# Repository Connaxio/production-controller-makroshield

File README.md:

# Production Controller makroShield
The Production Controller makroShield (PCM) is a modular controller designed to operate 24 V devices with the help of connected and remote sensors.

The PCM has a mikroBUS socket that works with Espoir, our Power over Ethernet devboard, to provide remote control, as well as advanced functionalities through node-red and Home Assistant. Simpler control can be achieved by directly programming Espoir.

Originally designed to operate greenhouses and irrigation valves, it can be adapted to many different kinds of small productions and climate control due to its modular nature.

2 drivers are available with the PCM: a 2-ways driver for bidirectional motors, and a 1-way, AC/DC controller for other devices, like valves, fans, and unidirectional motors. Up to 15 drivers can be connected simultaneously, and scheduled to use up to 350 Watts of power at a time.

Being modular makes the PCM easy to repair and upgrade, and helps reduce cost for smaller operations.

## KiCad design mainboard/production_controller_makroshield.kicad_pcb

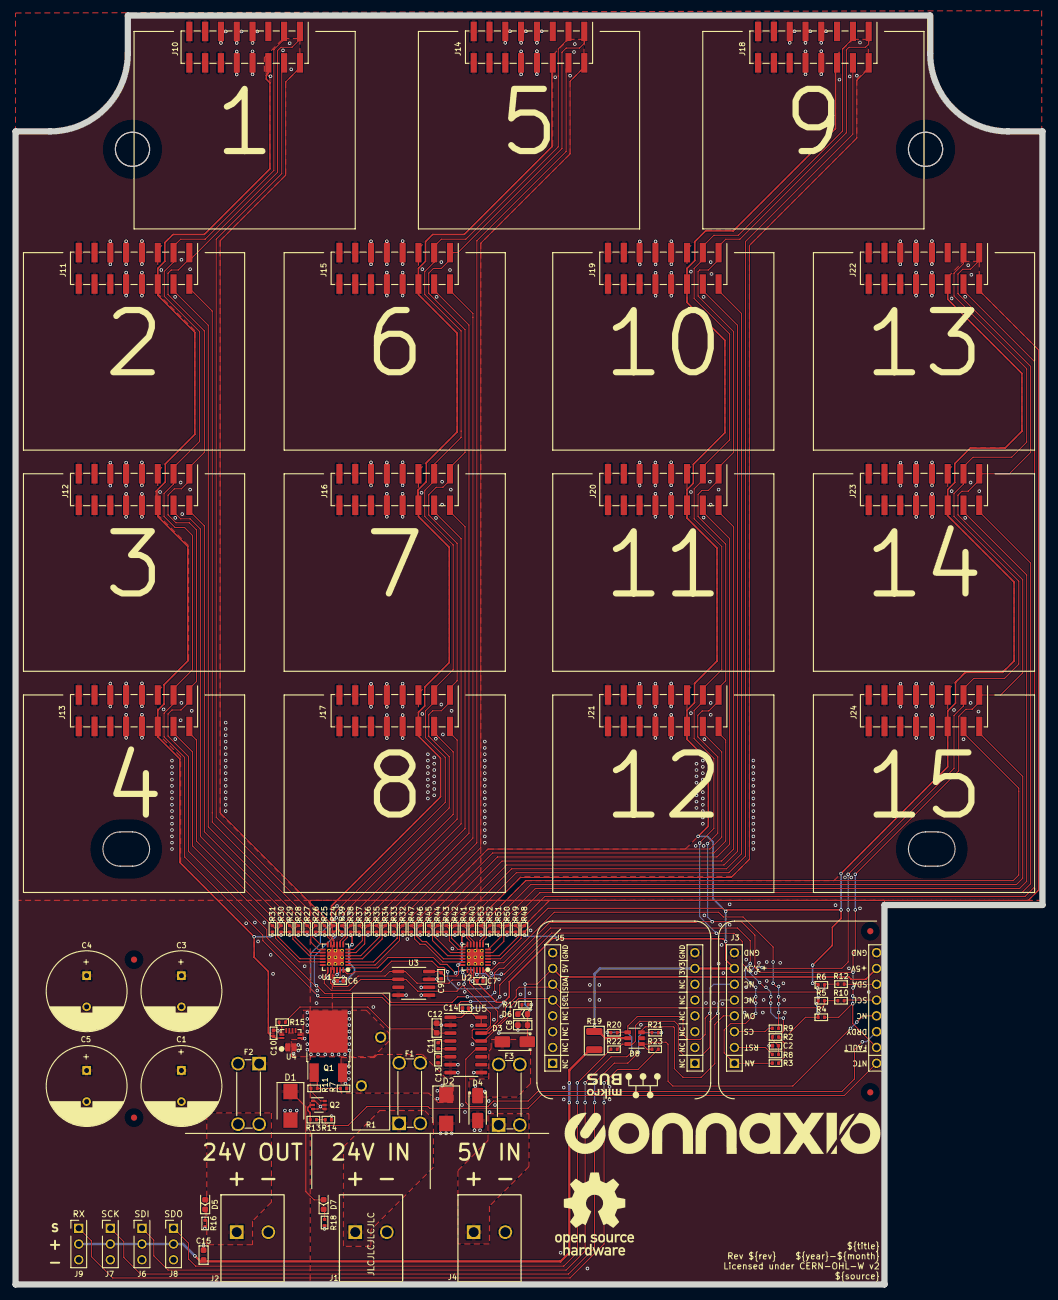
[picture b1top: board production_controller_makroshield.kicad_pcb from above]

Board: 2 copper layers, 165.1 x 204.0 mm, 118 parts (1 on the bottom side), 72 nets.

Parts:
C1, C3, C4, C5: CAP_AE_1MF_50V_TH_12.5MM; CAPAE_RAD_D12.5_H26.5_P5
C2, C6, C7, C9, C10, C11, C13, C14: CAP_CER_100NF_25V_0402; CAP_CER_0402_1005M
C8, C12, C15: CAP_CER_22UF_10V_0603; CAP_CER_0603_1608M
D1, D2: DIO_TVS_24V_UNI_SMB; DO-124AA_SMB
D3: DIO_SBD_100V_3A_SMA; DO-214AC_SMA
D4: DIO_TVS_5V_UNI_SMA; DO-214AC_SMA
D5, D6, D7: DIO_LED_GREEN_150060GS75000; LED_0603_1608M
D8: DIO_TVS_SRV05-4HTG; SOT-23-6
F1, F2, F3: FUS_BLADE_MINI_3588-1
F4, F5, F6, F7: FID_1X3
J1, J2, J4: CON_TERM_BLK_1X2_TB008A-508-02BE
J3: CON_HDR_MIKROBUS_ADDON_TH
J5: CON_HDR_MIKROBUS_SOCKET_TH
J6, J7, J8, J9: CON_HDR_100MILS_M_TH_1X3
J10, J11, J12, J13, J14, J15, J16, J17, J18, J19, J20, J21, J22, J23, J24: CON_CONNAXIO_MOTOR_DRIVER
MTH1, MTH2: MTH_M5_NPTH
MTH3, MTH4: MTH_SLOT_M5_2MM_NPTH
Q1: TRX_PMOS_AOD4189; TO-252-3
Q2: TRX_2NPN_BC846S,115; SOT-363_SC-70-6
R1: NTC_SL22 2R018; RV_DISC_D22_W6_P7.8
R2, R3, R4, R7, R11, R13, R14, R24, R25, R26, R27, R28, R29, R30, R31, R32, R33, R34, R35, R36, R37, R38, R39, R40, R41, R42, R43, R44, R45, R46, R47, R48, R49, R50, R51, R52, R53: RES_12.4KΩ_1%_0402; RES_0402_1005M
R5, R6, R15, R16, R18: RES_5.10KΩ_1%_0402; RES_0402_1005M
R8, R9, R10, R12, R20, R21, R22, R23: RES_226Ω_1%_0402; RES_0402_1005M
R17: RES_1.00KΩ_1%_0402; RES_0402_1005M
R19: PTC_SMD1210B010TF; RES_1210_3225M
U1, U2: IO_EXP_PI4IOE5V6416ZDEX; QFN-24_4x4_P0.5_EP2.7X2.7
U3: SEN_TEMP_TMP1075DR; SOIC-8_3.9x4.9_P1.27
U4: SEN_CUR_ACS711KEXLT-31AB-T; QFN-12_CUR_SEN_ACS7
U5: ADC_NAU7802SGI; SOIC-16_3.9X9.9_P1.27

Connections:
+3.3V: C6.1, C7.1, C9.1, C10.1, C14.1, D8.5, J3.7 (+3.3V), J5.7 (+3.3V), J10.6 (3.3V), J11.6 (3.3V), J12.6 (3.3V), J13.6 (3.3V), J14.6 (3.3V), J15.6 (3.3V), J16.6 (3.3V), J17.6 (3.3V), J18.6 (3.3V), J19.6 (3.3V), J20.6 (3.3V), J21.6 (3.3V), J22.6 (3.3V), J23.6 (3.3V), J24.6 (3.3V), R2.1, R3.1, R4.1, R5.1, R6.1, R19.1, R24.1, R25.1, R26.1, R27.1, R28.1, R29.1, R30.1, R31.1, R32.1, R33.1, R34.1, R35.1, R36.1, R37.1, R38.1, R39.1, R40.1, R41.1, R42.1, R43.1, R44.1, R45.1, R46.1, R47.1, R48.1, R49.1, R50.1, R51.1, R52.1, R53.1, U1.21 (VDDP), U1.23 (VDDI2C), U2.18 (ADDR), U2.21 (VDDP), U2.23 (VDDI2C), U3.8 (V+), U4.12 (VCC), U5.1 (REFP), U5.15 (DVDD), U5.16 (AVDD)
+5V: C8.1, D3.1 (K), D6.2 (A), J3.15 (+5V), J5.15 (+5V)
+24VDC: C1.1, C3.1, C4.1, C5.1, D1.1 (K), D7.2 (A), F2.1, F2.2, J10.12 (VDrive), J10.13 (VDrive), J10.14 (VDrive), J10.15 (VDrive), J10.16 (VDrive), J11.12 (VDrive), J11.13 (VDrive), J11.14 (VDrive), J11.15 (VDrive), J11.16 (VDrive), J12.12 (VDrive), J12.13 (VDrive), J12.14 (VDrive), J12.15 (VDrive), J12.16 (VDrive), J13.12 (VDrive), J13.13 (VDrive), J13.14 (VDrive), J13.15 (VDrive), J13.16 (VDrive), J14.12 (VDrive), J14.13 (VDrive), J14.14 (VDrive), J14.15 (VDrive), J14.16 (VDrive), J15.12 (VDrive), J15.13 (VDrive), J15.14 (VDrive), J15.15 (VDrive), J15.16 (VDrive), J16.12 (VDrive), J16.13 (VDrive), J16.14 (VDrive), J16.15 (VDrive), J16.16 (VDrive), J17.12 (VDrive), J17.13 (VDrive), J17.14 (VDrive), J17.15 (VDrive), J17.16 (VDrive), J18.12 (VDrive), J18.13 (VDrive), J18.14 (VDrive), J18.15 (VDrive), J18.16 (VDrive), J19.12 (VDrive), J19.13 (VDrive), J19.14 (VDrive), J19.15 (VDrive), J19.16 (VDrive), J20.12 (VDrive), J20.13 (VDrive), J20.14 (VDrive), J20.15 (VDrive), J20.16 (VDrive), J21.12 (VDrive), J21.13 (VDrive), J21.14 (VDrive), J21.15 (VDrive), J21.16 (VDrive), J22.12 (VDrive), J22.13 (VDrive), J22.14 (VDrive), J22.15 (VDrive), J22.16 (VDrive), J23.12 (VDrive), J23.13 (VDrive), J23.14 (VDrive), J23.15 (VDrive), J23.16 (VDrive), J24.12 (VDrive), J24.13 (VDrive), J24.14 (VDrive), J24.15 (VDrive), J24.16 (VDrive), U4.1 (IP+), U4.2 (IP+)
/24V_OUT: D5.2 (A), F2.3, F2.4, J2.1
/CS+: Q1.3 (D), R1.2, U4.3 (IP-), U4.4 (IP-)
/DRDY: J3.11 (TX), U5.12 (DRDY)
/I2C_SCL: J5.13 (SCL), R5.2, R10.2, U1.19 (SCL), U2.19 (SCL), U3.2 (SCL), U5.13 (SCLK)
/I2C_SDA: J5.14 (SDA), R6.2, R12.2, U1.20 (SDA), U2.20 (SDA), U3.1 (SDA), U5.14 (SDIO)
/INT_IO: J3.1 (AN), R3.2, U1.22 (~INT), U2.22 (~INT)
/IO_RX: D8.1, J3.12 (RX), R23.1
/IO_SCK: D8.3, J3.4 (SCK), R21.1
/IO_SDI: D8.4, J3.6 (SDI), R20.1
/IO_SDO: D8.6, J3.5 (SDO), R22.1
/NTC_BYPASS: J3.9 (PWM), R13.1, R14.1
/RST_IO: R9.1, U1.24 (~RESET), U2.24 (~RESET)
CTRLA1: J10.2 (~CTRLA), R24.2, U1.10 (P1_0)
CTRLA2: J11.2 (~CTRLA), R26.2, U1.12 (P1_2)
CTRLA3: J12.2 (~CTRLA), R28.2, U1.14 (P1_4)
CTRLA4: J13.2 (~CTRLA), R30.2, U1.16 (P1_6)
CTRLA5: J14.2 (~CTRLA), R32.2, U1.1 (P0_0)
CTRLA6: J15.2 (~CTRLA), R34.2, U1.3 (P0_2)
CTRLA7: J16.2 (~CTRLA), R36.2, U1.5 (P0_4)
CTRLA8: J17.2 (~CTRLA), R38.2, U1.7 (P0_6)
CTRLA9: J18.2 (~CTRLA), R40.2, U2.10 (P1_0)
CTRLA10: J19.2 (~CTRLA), R42.2, U2.12 (P1_2)
CTRLA11: J20.2 (~CTRLA), R44.2, U2.14 (P1_4)
CTRLA12: J21.2 (~CTRLA), R46.2, U2.16 (P1_6)
CTRLA13: J22.2 (~CTRLA), R48.2, U2.3 (P0_2)
CTRLA14: J23.2 (~CTRLA), R50.2, U2.5 (P0_4)
CTRLA15: J24.2 (~CTRLA), R52.2, U2.7 (P0_6)
CTRLB1: J10.4 (~CTRLB), R25.2, U1.11 (P1_1)
CTRLB2: J11.4 (~CTRLB), R27.2, U1.13 (P1_3)
CTRLB3: J12.4 (~CTRLB), R29.2, U1.15 (P1_5)
CTRLB4: J13.4 (~CTRLB), R31.2, U1.17 (P1_7)
CTRLB5: J14.4 (~CTRLB), R33.2, U1.2 (P0_1)
CTRLB6: J15.4 (~CTRLB), R35.2, U1.4 (P0_3)
CTRLB7: J16.4 (~CTRLB), R37.2, U1.6 (P0_5)
CTRLB8: J17.4 (~CTRLB), R39.2, U1.8 (P0_7)
CTRLB9: J18.4 (~CTRLB), R41.2, U2.11 (P1_1)
CTRLB10: J19.4 (~CTRLB), R43.2, U2.13 (P1_3)
CTRLB11: J20.4 (~CTRLB), R45.2, U2.15 (P1_5)
CTRLB12: J21.4 (~CTRLB), R47.2, U2.17 (P1_7)
CTRLB13: J22.4 (~CTRLB), R49.2, U2.4 (P0_3)
CTRLB14: J23.4 (~CTRLB), R51.2, U2.6 (P0_5)
CTRLB15: J24.4 (~CTRLB), R53.2, U2.8 (P0_7)
FAULT: J3.10 (INT), J10.1 (~FAULT), J11.1 (~FAULT), J12.1 (~FAULT), J13.1 (~FAULT), J14.1 (~FAULT), J15.1 (~FAULT), J16.1 (~FAULT), J17.1 (~FAULT), J18.1 (~FAULT), J19.1 (~FAULT), J20.1 (~FAULT), J21.1 (~FAULT), J22.1 (~FAULT), J23.1 (~FAULT), J24.1 (~FAULT), R4.2
GND: C1.2, C2.2, C3.2, C4.2, C5.2, C6.2, C7.2, C8.2, C9.2, C10.2, C12.2, C13.2, C14.2, C15.2, D1.2 (A), D2.2 (A), D4.2 (A), D8.2, J1.2, J2.2, J3.8 (GND), J3.16 (GND), J4.2, J5.8 (GND), J5.16 (GND), J6.3, J7.3, J8.3, J9.3, J10.7 (GND), J10.8 (GND), J10.9 (GND), J10.10 (GND), J10.11 (GND), J11.7 (GND), J11.8 (GND), J11.9 (GND), J11.10 (GND), J11.11 (GND), J12.7 (GND), J12.8 (GND), J12.9 (GND), J12.10 (GND), J12.11 (GND), J13.7 (GND), J13.8 (GND), J13.9 (GND), J13.10 (GND), J13.11 (GND), J14.7 (GND), J14.8 (GND), J14.9 (GND), J14.10 (GND), J14.11 (GND), J15.7 (GND), J15.8 (GND), J15.9 (GND), J15.10 (GND), J15.11 (GND), J16.7 (GND), J16.8 (GND), J16.9 (GND), J16.10 (GND), J16.11 (GND), J17.7 (GND), J17.8 (GND), J17.9 (GND), J17.10 (GND), J17.11 (GND), J18.7 (GND), J18.8 (GND), J18.9 (GND), J18.10 (GND), J18.11 (GND), J19.7 (GND), J19.8 (GND), J19.9 (GND), J19.10 (GND), J19.11 (GND), J20.7 (GND), J20.8 (GND), J20.9 (GND), J20.10 (GND), J20.11 (GND), J21.7 (GND), J21.8 (GND), J21.9 (GND), J21.10 (GND), J21.11 (GND), J22.7 (GND), J22.8 (GND), J22.9 (GND), J22.10 (GND), J22.11 (GND), J23.7 (GND), J23.8 (GND), J23.9 (GND), J23.10 (GND), J23.11 (GND), J24.7 (GND), J24.8 (GND), J24.9 (GND), J24.10 (GND), J24.11 (GND), Q2.1 (E1), Q2.3 (C2), Q2.4 (E2), Q2.5 (B2), R14.2, R16.2, R17.2, R18.2, U1.9 (VSS), U1.18 (ADDR), U1.25 (PAD), U2.9 (VSS), U2.25 (PAD), U3.4 (GND), U3.5 (A2), U3.6 (A1), U3.7 (A0), U4.5 (GND), U5.2 (VIN1N), U5.7 (REFN), U5.8 (AVSS), U5.9 (DVSS)
unnamed: C11.1, U5.5 (VIN2P)
unnamed: C11.2, U5.4 (VIN2N)
unnamed: C12.1, R15.2, U5.3 (VIN1P)
unnamed: C13.1, U5.6 (VBG)
unnamed: D2.1 (K), F1.3, F1.4, Q1.2 (S), R1.1, R7.1
unnamed: D3.2 (A), D4.1 (K), F3.3, F3.4
unnamed: D5.1 (K), R16.1
unnamed: D6.1 (K), R17.1
unnamed: D7.1 (K), R18.1
unnamed: F1.1, F1.2, J1.1
unnamed: F3.1, F3.2, J4.1
unnamed: J3.2 (RST), R8.2
unnamed: J3.3 (CS), R9.2
unnamed: J3.13 (SCL), R10.1
unnamed: J3.14 (SDA), R12.1
unnamed: J6.1, R20.2
unnamed: J7.1, R21.2
unnamed: J8.1, R22.2
unnamed: C15.1, J6.2, J7.2, J8.2, J9.2, R19.2
unnamed: J9.1, R23.2
unnamed: Q1.1 (G), R7.2, R11.1
unnamed: Q2.2 (B1), R13.2
unnamed: Q2.6 (C1), R11.2
unnamed: R15.1, U4.11 (VIOUT)
RST_MOT: C2.1, J10.3 (~RESET), J11.3 (~RESET), J12.3 (~RESET), J13.3 (~RESET), J14.3 (~RESET), J15.3 (~RESET), J16.3 (~RESET), J17.3 (~RESET), J18.3 (~RESET), J19.3 (~RESET), J20.3 (~RESET), J21.3 (~RESET), J22.3 (~RESET), J23.3 (~RESET), J24.3 (~RESET), R2.2, R8.1

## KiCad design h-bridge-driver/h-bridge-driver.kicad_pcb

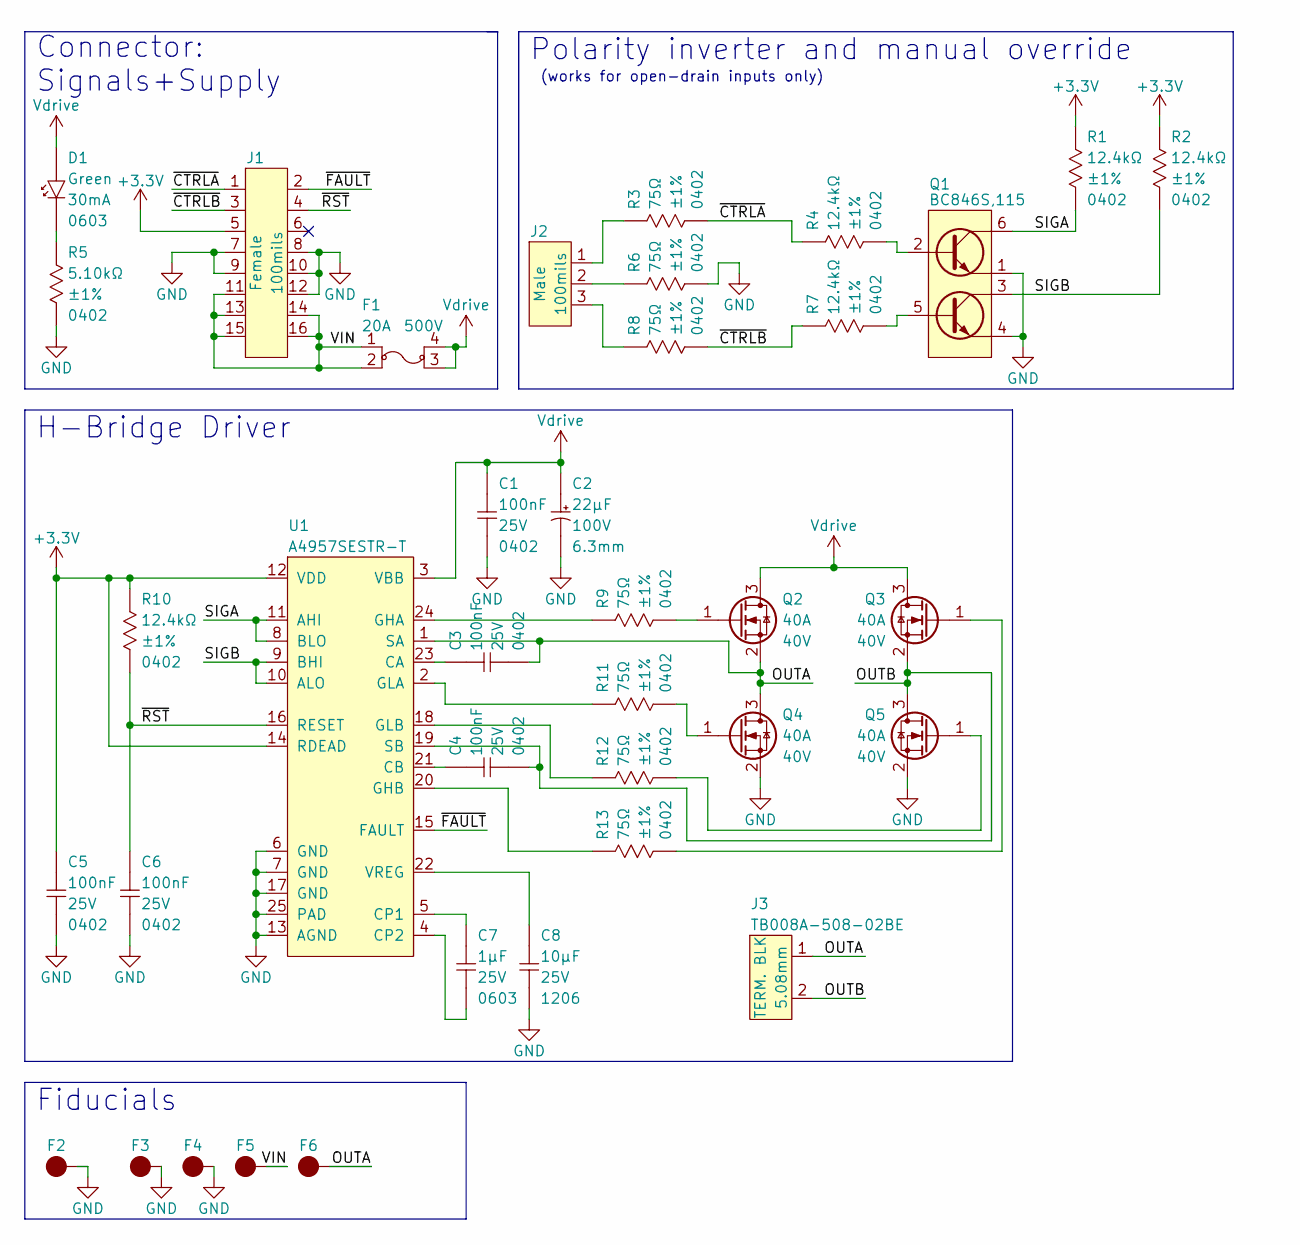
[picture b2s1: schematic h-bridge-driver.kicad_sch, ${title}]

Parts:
C1, C3, C4, C5, C6: CAP_CER_100NF_25V_0402; CAP_CER_0402_1005M; Tolerance ±10%; Voltage 25V; Manufacturer Part Number CL05A104KA5NNNC
C2: CAP_AE_22UF_100V_TH_6.3MM; CAP_AE_RAD_D6.3_H12.5_P2.5; Tolerance ±20%; Voltage 100V; Manufacturer Part Number ESK226M100AE3AA
C7: CAP_CER_1UF_25V_0603; CAP_CER_0603_1608M; Tolerance ±10%; Voltage 25V; Manufacturer Part Number CL10A105KA8NNNC
C8: CAP_CER_10UF_25V_1206; CAP_CER_1206_3216M; Tolerance ±10%; Voltage 25V; Manufacturer Part Number CL31A106KAHNNNE
D1: DIO_LED_GREEN_150060GS75000; LED_0603_1608M; Manufacturer Part Number 150060GS75000
F1: FUS_BLADE_MINI_3588-1; Voltage 500V; Manufacturer Part Number 3588-1
F2, F3, F4, F5, F6: FID_1X1
J1: CON_HDR_100MILS_F_TH_2X8; Voltage 350V
J2: CON_HDR_100MILS_M_TH_1X3; Voltage 350V
J3: CON_TERM_BLK_1X2_TB008A-508-02BE; Voltage 300V; Manufacturer Part Number TB008A-508-02BE
Q1: TRX_2NPN_BC846S,115; SOT-363_SC-70-6; Voltage 65V; Manufacturer Part Number BC846S,115
Q2, Q3, Q4, Q5: TRX_NMOS_PJD40N04_L2_00001; TO-252-3; Voltage 40V; Manufacturer Part Number PJD40N04_L2_00001
R1, R2, R4, R7, R10: RES_12.4KΩ_1%_0402; RES_0402_1005M; Tolerance ±1%; Voltage 50V; Manufacturer Part Number RMCF0402FT12K4
R3, R6, R8, R9, R11, R12, R13: RES_226Ω_1%_0402; RES_0402_1005M; Tolerance ±1%; Voltage 50V; Manufacturer Part Number RMCF0402FT75R0
R5: RES_5.10KΩ_1%_0402; RES_0402_1005M; Tolerance ±1%; Voltage 50V; Manufacturer Part Number RMCF0402FT5K10
U1: DRV_A4957SESTR-T; QFN-24_4x4_P0.5_EP2.7X2.7; Voltage 50V; Manufacturer Part Number A4957SESTR-T

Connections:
+3.3V: C5.1, J1.5, R1.1, R2.1, R10.1, U1.12 (VDD), U1.14 (RDEAD)
/OUTA: C3.2, F6.1, J3.1, Q2.2 (S), Q4.3 (D), U1.1 (SA)
/OUTB: C4.2, J3.2, Q3.2 (S), Q5.3 (D), U1.19 (SB)
/SIGA: Q1.6 (C1), R1.2, U1.8 (BLO), U1.11 (AHI)
/SIGB: Q1.3 (C2), R2.2, U1.9 (BHI), U1.10 (ALO)
/VIN: F1.1, F1.2, F5.1, J1.11, J1.13, J1.14, J1.15, J1.16
/~CTRLA: J1.1, R3.2, R4.1
/~CTRLB: J1.3, R7.1, R8.2
/~FAULT: J1.2, U1.15 (FAULT)
/~RST: C6.1, J1.4, R10.2, U1.16 (RESET)
GND: C1.2, C2.2, C5.2, C6.2, C8.2, F2.1, F3.1, F4.1, J1.7, J1.8, J1.9, J1.10, J1.12, Q1.1 (E1), Q1.4 (E2), Q4.2 (S), Q5.2 (S), R5.2, R6.2, U1.6 (GND), U1.7 (GND), U1.13 (AGND), U1.17 (GND), U1.25 (PAD)
unnamed: C3.1, U1.23 (CA)
unnamed: C4.1, U1.21 (CB)
unnamed: C7.1, U1.5 (CP1)
unnamed: C7.2, U1.4 (CP2)
unnamed: C8.1, U1.22 (VREG)
unnamed: D1.1 (K), R5.1
unnamed: J2.1, R3.1
unnamed: J2.2, R6.1
unnamed: J2.3, R8.1
unnamed: Q1.2 (B1), R4.2
unnamed: Q1.5 (B2), R7.2
unnamed: Q2.1 (G), R9.2
unnamed: Q3.1 (G), R13.2
unnamed: Q4.1 (G), R11.2
unnamed: Q5.1 (G), R12.2
unnamed: R9.1, U1.24 (GHA)
unnamed: R11.1, U1.2 (GLA)
unnamed: R12.1, U1.18 (GLB)
unnamed: R13.1, U1.20 (GHB)
Vdrive: C1.1, C2.1, D1.2 (A), F1.3, F1.4, Q2.3 (D), Q3.3 (D), U1.3 (VBB)

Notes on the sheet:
Fiducials
Polarity inverter and manual override
H-Bridge Driver
Connector: Signals+Supply
(works for open-drain inputs only)

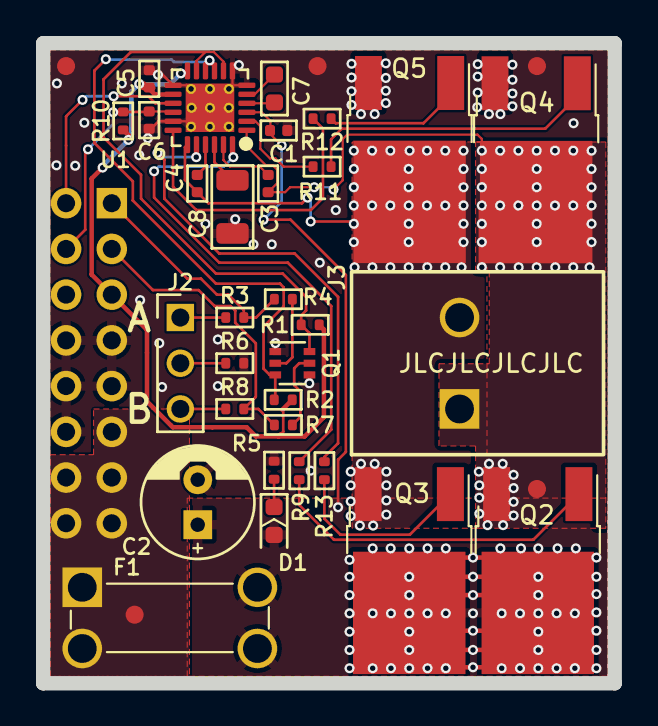
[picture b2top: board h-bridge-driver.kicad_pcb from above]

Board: 2 copper layers, 31.8 x 35.6 mm, 37 parts (1 on the bottom side), 31 nets.

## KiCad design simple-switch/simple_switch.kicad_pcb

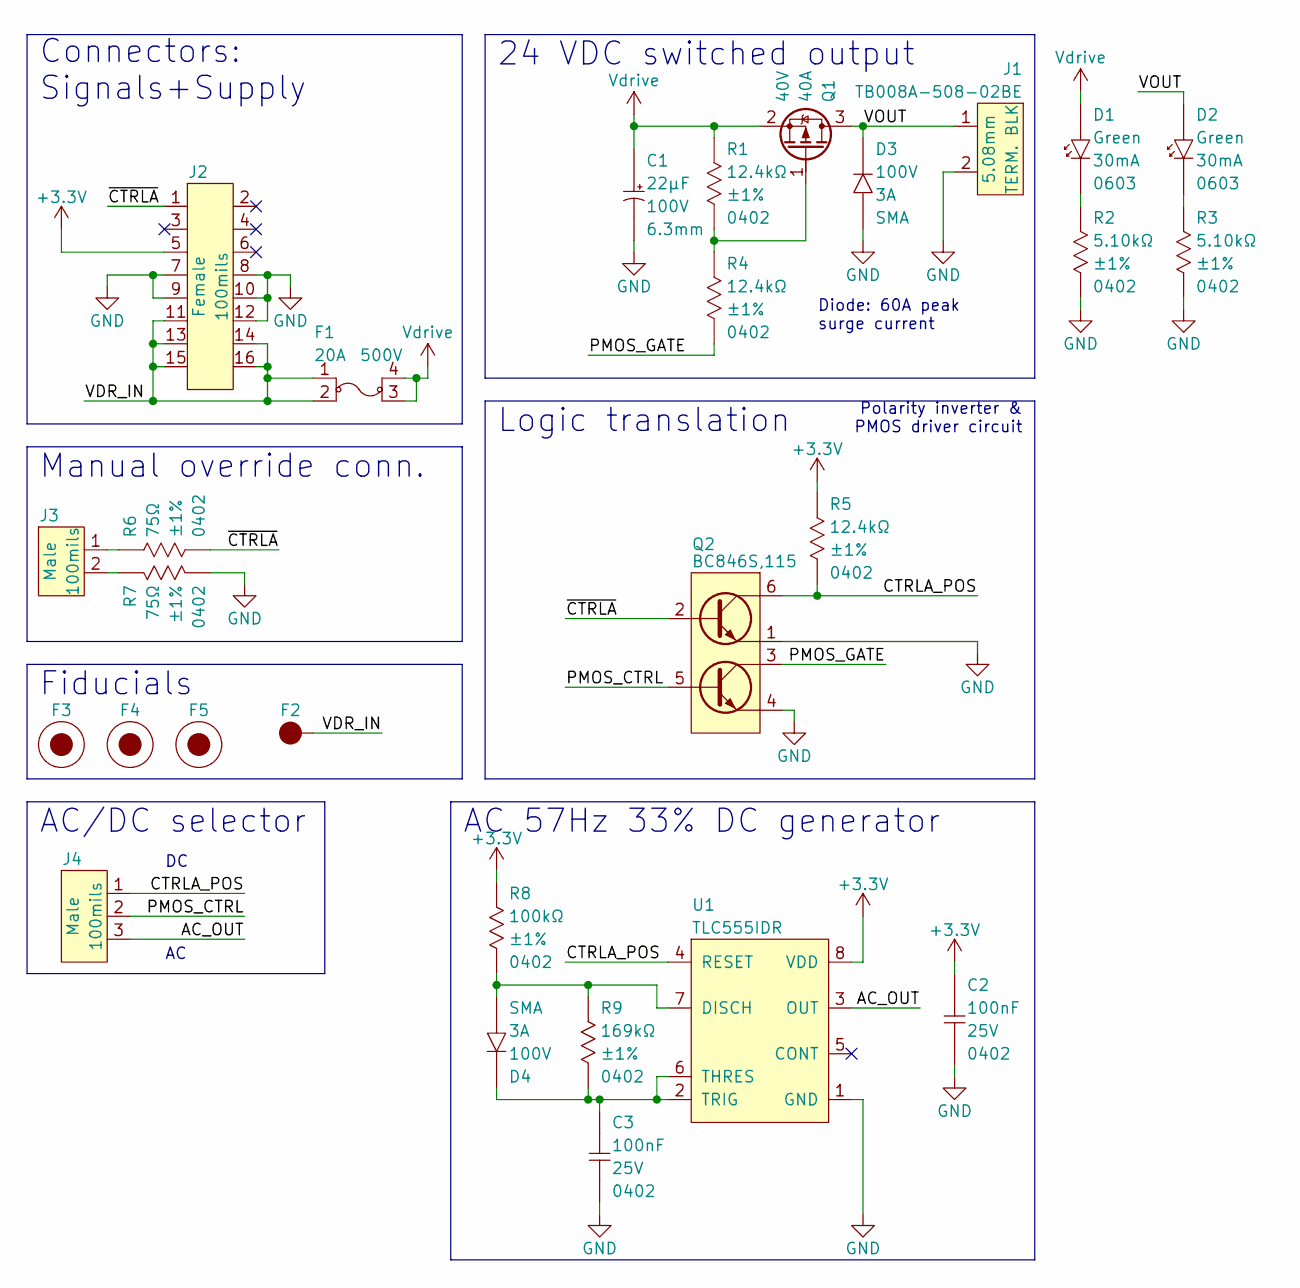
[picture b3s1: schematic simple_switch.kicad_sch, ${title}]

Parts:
C1: CAP_AE_22UF_100V_TH_6.3MM; CAP_AE_RAD_D6.3_H12.5_P2.5; Tolerance ±20%; Voltage 100V; Manufacturer Part Number ESK226M100AE3AA
C2, C3: CAP_CER_100NF_25V_0402; CAP_CER_0402_1005M; Tolerance ±10%; Voltage 25V; Manufacturer Part Number CL05A104KA5NNNC
D1, D2: DIO_LED_GREEN_150060GS75000; LED_0603_1608M; Manufacturer Part Number 150060GS75000
D3, D4: DIO_SBD_100V_3A_SMA; DO-214AC_SMA; Tolerance 60A; Voltage 100V; Manufacturer Part Number SL310A-TP
F1: FUS_BLADE_MINI_3588-1; Voltage 500V; Manufacturer Part Number 3588-1
F2: FID_1X1
F3, F4, F5: FID_1X3
J1: CON_TERM_BLK_1X2_TB008A-508-02BE; Voltage 300V; Manufacturer Part Number TB008A-508-02BE
J2: CON_HDR_100MILS_F_TH_2X8; Voltage 350V
J3: CON_HDR_100MILS_M_TH_1X2; Voltage 350V
J4: CON_HDR_100MILS_M_TH_1X3; Voltage 350V
Q1: TRX_PMOS_AOD4189; TO-252-3; Voltage 40V; Manufacturer Part Number AOD4189
Q2: TRX_2NPN_BC846S,115; SOT-363_SC-70-6; Voltage 65V; Manufacturer Part Number BC846S,115
R1, R4, R5: RES_12.4KΩ_1%_0402; RES_0402_1005M; Tolerance ±1%; Voltage 50V; Manufacturer Part Number RMCF0402FT12K4
R2, R3: RES_5.10KΩ_1%_0402; RES_0402_1005M; Tolerance ±1%; Voltage 50V; Manufacturer Part Number RMCF0402FT5K10
R6, R7: RES_226Ω_1%_0402; RES_0402_1005M; Tolerance ±1%; Voltage 50V; Manufacturer Part Number RMCF0402FT75R0
R8: RES_100KΩ_1%_0402; RES_0402_1005M; Tolerance ±1%; Voltage 50V; Manufacturer Part Number RMCF0402FT100K
R9: RES_169KΩ_1%_0402; RES_0402_1005M; Tolerance ±1%; Voltage 50V; Manufacturer Part Number RMCF0402FT169K
U1: TIMER_TLC555IDR; SOIC-8_3.9x4.9_P1.27; Voltage 3V - 15V; Manufacturer Part Number TLC555IDR

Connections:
+3.3V: C2.1, J2.5, R5.1, R8.1, U1.8 (VDD)
/AC_OUT: J4.3, U1.3 (OUT)
/CTRLA_POS: J4.1, Q2.6 (C1), R5.2, U1.4 (RESET)
/PMOS_CTRL: J4.2, Q2.5 (B2)
/PMOS_GATE: Q2.3 (C2), R4.2
/VDR_IN: F1.1, F1.2, F2.1, J2.11, J2.13, J2.14, J2.15, J2.16
/VOUT: D2.2 (A), D3.1 (K), J1.1, Q1.3 (D)
/~CTRLA: J2.1, Q2.2 (B1), R6.2
GND: C1.2, C2.2, C3.2, D3.2 (A), J1.2, J2.7, J2.8, J2.9, J2.10, J2.12, Q2.1 (E1), Q2.4 (E2), R2.2, R3.2, R7.2, U1.1 (GND)
unnamed: C3.1, D4.1 (K), R9.2, U1.2 (TRIG), U1.6 (THRES)
unnamed: D1.1 (K), R2.1
unnamed: D2.1 (K), R3.1
unnamed: D4.2 (A), R8.2, R9.1, U1.7 (DISCH)
unnamed: J3.1, R6.1
unnamed: J3.2, R7.1
unnamed: Q1.1 (G), R1.2, R4.1
Vdrive: C1.1, D1.2 (A), F1.3, F1.4, Q1.2 (S), R1.1

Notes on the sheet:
AC 57Hz 33% DC generator
Diode: 60A peak surge current
Polarity inverter & PMOS driver circuit
Logic translation
AC/DC selector
DC AC
Manual override conn.
Fiducials
24 VDC switched output
Connectors: Signals+Supply

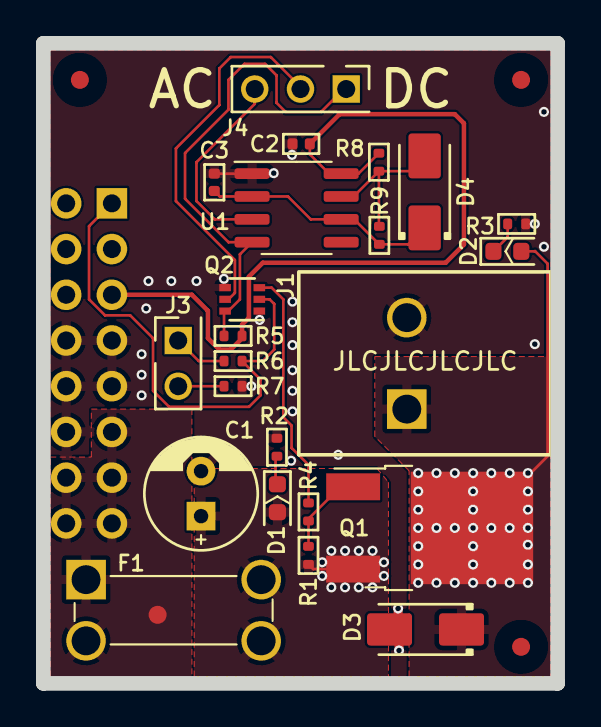
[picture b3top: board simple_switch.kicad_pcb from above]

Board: 2 copper layers, 28.6 x 35.6 mm, 28 parts (1 on the bottom side), 17 nets.

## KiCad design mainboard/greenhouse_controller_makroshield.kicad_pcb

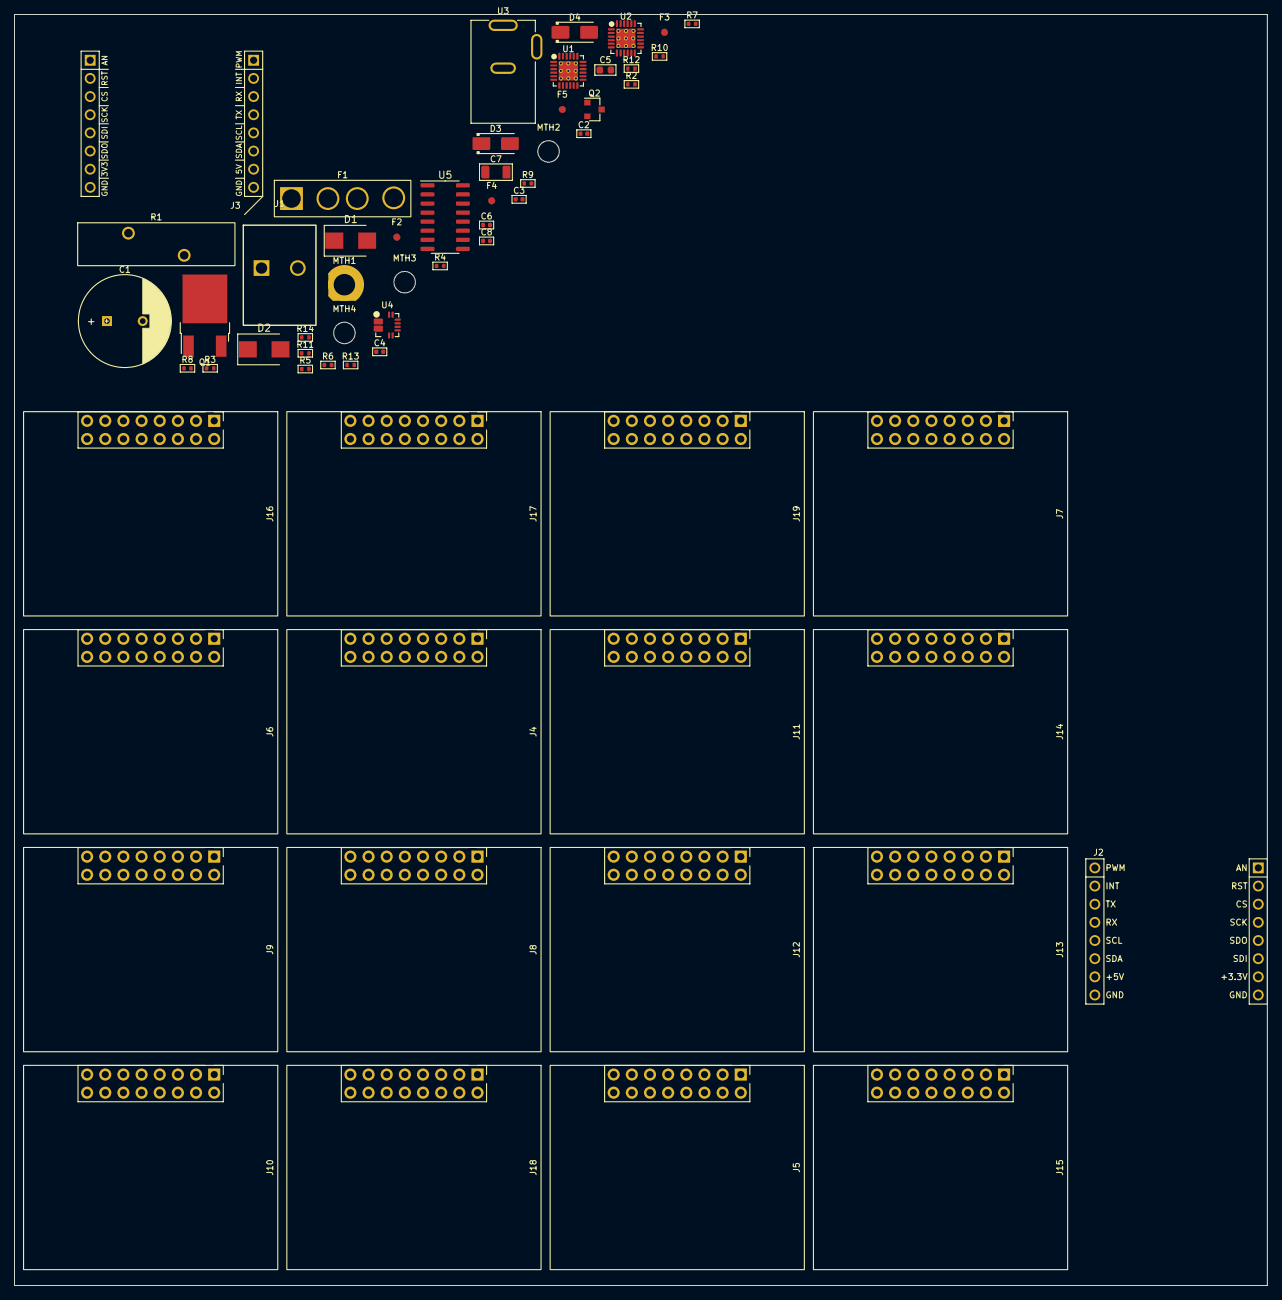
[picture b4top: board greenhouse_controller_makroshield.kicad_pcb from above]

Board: 2 copper layers, 175.3 x 177.8 mm, 61 parts (1 on the bottom side), 57 nets, no tracks yet.

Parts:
C1: CAP_AE_1MF_50V_TH_12.5MM; CAPAE_RAD_D12.5_H26.5_P5
C2, C3, C4, C6, C8: CAP_CER_100NF_25V_0402; CAP_CER_0402_1005M
C5: CAP_CER_22UF_10V_0603; CAP_CER_0603_1608M
C7: CAP_CER_10UF_25V_1206; CAP_CER_1206_3216M
D1, D2: DIO_TVS_24V_UNI_SMB; DO-124AA_SMB
D3: DIO_SBD_100V_3A_SMA; DO-214AC_SMA
D4: DIO_TVS_5V_UNI_SMA; DO-214AC_SMA
F1: FUS_BLADE_3522
F2, F3, F4, F5: FID_1X3
J1: CON_TERM_BLK_1X2_TB008A-508-02BE
J2: CON_HDR_MIKROBUS_ADDON_TH
J3: CON_HDR_MIKROBUS_SOCKET_TH
J4, J5, J6, J7, J8, J9, J10, J11, J12, J13, J14, J15, J16, J17, J18, J19: CON_CONNAXIO_MOTOR_DRIVER
MTH1: MTH_M2.5_PTH_CORNER
MTH2, MTH3, MTH4: MTH_M2.5_NPTH
Q1: TRX_PMOS_AOD4189; TO-252-3
Q2: TRX_NPN_MMBT3904-TP; SOT-23-3
R1: NTC_SL22 2R018; RV_DISC_D22_W6_P7.8
R2, R3, R4, R7, R10, R12, R14: RES_12.4KΩ_1%_0402; RES_0402_1005M
R5, R6, R11: RES_1.54KΩ_1%_0402; RES_0402_1005M
R8, R9: RES_226Ω_1%_0402; RES_0402_1005M
R13: RES_0Ω_0402; RES_0402_1005M
U1, U2: IO_EXP_PI4IOE5V6416ZDEX; QFN-24_4x4_P0.5_EP2.7X2.7
U3: CON_BARREL_2.1X5.5_PJ-002A
U4: SUN_CUR_ACS711KEXLT-31AB-T; QFN-12_CUR_SEN_ACS7
U5: ADC_NAU7802SGI; SOIC-16_3.9X9.9_P1.27

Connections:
+3.3V: C3.1, C4.1, C6.1, J2.7 (+3.3V), J3.7 (+3.3V), J4.6 (3.3V), J5.6 (3.3V), J6.6 (3.3V), J7.6 (3.3V), J8.6 (3.3V), J9.6 (3.3V), J10.6 (3.3V), J11.6 (3.3V), J12.6 (3.3V), J13.6 (3.3V), J14.6 (3.3V), J15.6 (3.3V), J16.6 (3.3V), J17.6 (3.3V), J18.6 (3.3V), J19.6 (3.3V), R2.1, R3.1, R4.1, R5.1, R6.1, U1.21 (VDDP), U1.23 (VDDI2C), U2.18 (ADDR), U2.21 (VDDP), U2.23 (VDDI2C), U4.12 (VCC), U5.1 (REFP), U5.15 (DVDD), U5.16 (AVDD)
+5V: C5.1, D3.1 (K), D4.1 (K), J2.15 (+5V), J3.15 (+5V)
+24VDC: C1.1, D1.1 (K), J4.12 (VDrive), J4.13 (VDrive), J4.14 (VDrive), J4.15 (VDrive), J4.16 (VDrive), J5.12 (VDrive), J5.13 (VDrive), J5.14 (VDrive), J5.15 (VDrive), J5.16 (VDrive), J6.12 (VDrive), J6.13 (VDrive), J6.14 (VDrive), J6.15 (VDrive), J6.16 (VDrive), J7.12 (VDrive), J7.13 (VDrive), J7.14 (VDrive), J7.15 (VDrive), J7.16 (VDrive), J8.12 (VDrive), J8.13 (VDrive), J8.14 (VDrive), J8.15 (VDrive), J8.16 (VDrive), J9.12 (VDrive), J9.13 (VDrive), J9.14 (VDrive), J9.15 (VDrive), J9.16 (VDrive), J10.12 (VDrive), J10.13 (VDrive), J10.14 (VDrive), J10.15 (VDrive), J10.16 (VDrive), J11.12 (VDrive), J11.13 (VDrive), J11.14 (VDrive), J11.15 (VDrive), J11.16 (VDrive), J12.12 (VDrive), J12.13 (VDrive), J12.14 (VDrive), J12.15 (VDrive), J12.16 (VDrive), J13.12 (VDrive), J13.13 (VDrive), J13.14 (VDrive), J13.15 (VDrive), J13.16 (VDrive), J14.12 (VDrive), J14.13 (VDrive), J14.14 (VDrive), J14.15 (VDrive), J14.16 (VDrive), J15.12 (VDrive), J15.13 (VDrive), J15.14 (VDrive), J15.15 (VDrive), J15.16 (VDrive), J16.12 (VDrive), J16.13 (VDrive), J16.14 (VDrive), J16.15 (VDrive), J16.16 (VDrive), J17.12 (VDrive), J17.13 (VDrive), J17.14 (VDrive), J17.15 (VDrive), J17.16 (VDrive), J18.12 (VDrive), J18.13 (VDrive), J18.14 (VDrive), J18.15 (VDrive), J18.16 (VDrive), J19.12 (VDrive), J19.13 (VDrive), J19.14 (VDrive), J19.15 (VDrive), J19.16 (VDrive), Q1.3 (D), R1.2
/24V_Neg: J1.2, U4.3 (IP-), U4.4 (IP-)
/DRDY: J2.11 (TX), U5.12 (DRDY)
/I2C_SCL: J2.13 (SCL), J3.13 (SCL), R5.2, U1.19 (SCL), U2.19 (SCL), U5.13 (SCLK)
/I2C_SDA: J2.14 (SDA), J3.14 (SDA), R6.2, U1.20 (SDA), U2.20 (SDA), U5.14 (SDIO)
/INT_IO: J2.1 (AN), R3.2, U1.22 (~INT), U2.22 (~INT)
/NTC_BYPASS: J2.9 (PWM), R11.1, R12.1
/RST_IO: R9.1, U1.24 (~RESET), U2.24 (~RESET)
CTRLA1: J4.2 (CTRLA), U1.1 (P0_0)
CTRLA2: J5.2 (CTRLA), U1.3 (P0_2)
CTRLA3: J6.2 (CTRLA), U1.5 (P0_4)
CTRLA4: J7.2 (CTRLA), U1.7 (P0_6)
CTRLA5: J8.2 (CTRLA), U1.10 (P1_0)
CTRLA6: J9.2 (CTRLA), U1.12 (P1_2)
CTRLA7: J10.2 (CTRLA), U1.14 (P1_4)
CTRLA8: J11.2 (CTRLA), U1.16 (P1_6)
CTRLA9: J12.2 (CTRLA), U2.1 (P0_0)
CTRLA10: J13.2 (CTRLA), U2.3 (P0_2)
CTRLA11: J14.2 (CTRLA), U2.5 (P0_4)
CTRLA12: J15.2 (CTRLA), U2.7 (P0_6)
CTRLA13: J16.2 (CTRLA), U2.10 (P1_0)
CTRLA14: J17.2 (CTRLA), U2.12 (P1_2)
CTRLA15: J18.2 (CTRLA), U2.14 (P1_4)
CTRLA16: J19.2 (CTRLA), U2.16 (P1_6)
CTRLB1: J4.4 (CTRLB), U1.2 (P0_1)
CTRLB2: J5.4 (CTRLB), U1.4 (P0_3)
CTRLB3: J6.4 (CTRLB), U1.6 (P0_5)
CTRLB4: J7.4 (CTRLB), U1.8 (P0_7)
CTRLB5: J8.4 (CTRLB), U1.11 (P1_1)
CTRLB6: J9.4 (CTRLB), U1.13 (P1_3)
CTRLB7: J10.4 (CTRLB), U1.15 (P1_5)
CTRLB8: J11.4 (CTRLB), U1.17 (P1_7)
CTRLB9: J12.4 (CTRLB), U2.2 (P0_1)
CTRLB10: J13.4 (CTRLB), U2.4 (P0_3)
CTRLB11: J14.4 (CTRLB), U2.6 (P0_5)
CTRLB12: J15.4 (CTRLB), U2.8 (P0_7)
CTRLB13: J16.4 (CTRLB), U2.11 (P1_1)
CTRLB14: J17.4 (CTRLB), U2.13 (P1_3)
CTRLB15: J18.4 (CTRLB), U2.15 (P1_5)
CTRLB16: J19.4 (CTRLB), U2.17 (P1_7)
FAULT: J2.10 (INT), J4.1 (FAULT), J5.1 (FAULT), J6.1 (FAULT), J7.1 (FAULT), J8.1 (FAULT), J9.1 (FAULT), J10.1 (FAULT), J11.1 (FAULT), J12.1 (FAULT), J13.1 (FAULT), J14.1 (FAULT), J15.1 (FAULT), J16.1 (FAULT), J17.1 (FAULT), J18.1 (FAULT), J19.1 (FAULT), R4.2
GND: C1.2, C2.2, C3.2, C4.2, C5.2, C6.2, C7.2, C8.2, D1.2 (A), D2.2 (A), D4.2 (A), J2.8 (GND), J2.16 (GND), J3.8 (GND), J3.16 (GND), J4.7 (GND), J4.8 (GND), J4.9 (GND), J4.10 (GND), J4.11 (GND), J5.7 (GND), J5.8 (GND), J5.9 (GND), J5.10 (GND), J5.11 (GND), J6.7 (GND), J6.8 (GND), J6.9 (GND), J6.10 (GND), J6.11 (GND), J7.7 (GND), J7.8 (GND), J7.9 (GND), J7.10 (GND), J7.11 (GND), J8.7 (GND), J8.8 (GND), J8.9 (GND), J8.10 (GND), J8.11 (GND), J9.7 (GND), J9.8 (GND), J9.9 (GND), J9.10 (GND), J9.11 (GND), J10.7 (GND), J10.8 (GND), J10.9 (GND), J10.10 (GND), J10.11 (GND), J11.7 (GND), J11.8 (GND), J11.9 (GND), J11.10 (GND), J11.11 (GND), J12.7 (GND), J12.8 (GND), J12.9 (GND), J12.10 (GND), J12.11 (GND), J13.7 (GND), J13.8 (GND), J13.9 (GND), J13.10 (GND), J13.11 (GND), J14.7 (GND), J14.8 (GND), J14.9 (GND), J14.10 (GND), J14.11 (GND), J15.7 (GND), J15.8 (GND), J15.9 (GND), J15.10 (GND), J15.11 (GND), J16.7 (GND), J16.8 (GND), J16.9 (GND), J16.10 (GND), J16.11 (GND), J17.7 (GND), J17.8 (GND), J17.9 (GND), J17.10 (GND), J17.11 (GND), J18.7 (GND), J18.8 (GND), J18.9 (GND), J18.10 (GND), J18.11 (GND), J19.7 (GND), J19.8 (GND), J19.9 (GND), J19.10 (GND), J19.11 (GND), Q2.2 (E), R12.2, R13.2, U1.9 (VSS), U1.18 (ADDR), U1.25 (PAD), U2.9 (VSS), U2.25 (PAD), U3.2, U3.3, U4.1 (IP+), U4.2 (IP+), U4.5 (GND), U5.2 (VIN1N), U5.4 (VIN2N), U5.5 (VIN2P), U5.7 (REFN), U5.8 (AVSS), U5.9 (DVSS)
unnamed: C7.1, R14.2, U5.3 (VIN1P)
unnamed: C8.1, U5.6 (VBG)
unnamed: D2.1 (K), F1.3, F1.4, Q1.2 (S), R1.1, R7.1
unnamed: D3.2 (A), U3.1
unnamed: F1.1, F1.2, J1.1
unnamed: J2.2 (RST), R8.2
unnamed: J2.3 (CS), R9.2
unnamed: MTH1.1, R13.1
unnamed: Q1.1 (G), R7.2, R10.1
unnamed: Q2.1 (B), R11.2
unnamed: Q2.3 (C), R10.2
unnamed: R14.1, U4.11 (VIOUT)
RST_MOT: C2.1, J4.3 (RESET), J5.3 (RESET), J6.3 (RESET), J7.3 (RESET), J8.3 (RESET), J9.3 (RESET), J10.3 (RESET), J11.3 (RESET), J12.3 (RESET), J13.3 (RESET), J14.3 (RESET), J15.3 (RESET), J16.3 (RESET), J17.3 (RESET), J18.3 (RESET), J19.3 (RESET), R2.2, R8.1

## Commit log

2023-01-18 Add license,create project
2023-01-19 WIP, add conntectors
2023-01-19 Finish 24VDC input
2023-01-20 Finish motor driver and add tentative switched output (TBC with valves)
2023-01-20 Split project in two parts: mainboard and motor driver boards
2023-01-22 Complete H bridge driver
2023-01-23 Add IO expanders, add simple PMOS switch, add 5V TVS,
2023-01-23 Add motor driver page and I2C proteciton adapter, current & temp sensor
2023-01-24 Move fuse to motor driver board Optimize board array schematic (hierarchical schematics)
2023-01-25 rename project, comple simple switch layout, fix thermal reliefs
2023-01-29 Inverted motor controls for open-drain operation and manual switch override compatibility
2023-01-31 Position drive rmodules, choose enclosure, shape PCB
2023-02-01 Routing mainboard
2023-02-02 Routing
2023-02-02 DRC pass
2023-02-14 Add high-current pathways and extra capacitors. DRC pass
2023-02-14 Add LEDs, fix NMOS, Add logos and infos on PCBs.
2023-03-01 Add Enclosure piercing guide and fix h-bridge-driver NMOS pads.
2023-03-05 Invert connectors (male/female) Replace TH connectors with SMD ones on mainboard Add 555 timer on simple-switch to generate 60 Hz Add jumper on simple-switch to select AC Add series I2C resistors on 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
2023-03-06 Add flyback diode to simple-switch
2023-03-06 Add onboard temperature sensor Add connector for Analog / 1-wire / PWM sensor
2023-03-06 Add filter cap to current reading ADC
2023-03-31 Add 4 extra IOs (SVG connectors)

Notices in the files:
h-bridge-driver/h-bridge-driver.kicad_pcb:
Licensed under CERN-OHL-W v2
simple-switch/simple_switch.kicad_pcb:
CERN-OHL-W v2
